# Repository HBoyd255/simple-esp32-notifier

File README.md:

# Simple ESP32 Notifier

This is just a simple board to hold a
[Heltec WiFi Kit 32](https://heltec.org/project/wifi-kit32-v3/) ESP32 dev kit.

The board works for either the V2 or V3 boards, but require different pin
definitions due to the different pinouts of the boards. Pin definitions can be
found in [pinDefs_V2.h](reference/pinDefs_V2.h) and
[pinDefs_V3.h](reference/pinDefs_V3.h).

This Heltec board comes with a built in 0.96 OLED screen that is used for
showing notifications, and the board adds 3 LEDs and 3 Buttons.

As this board is designed to be simple it just uses through hole components and
uses one GPIO pin per LED and one per button.

# Photos

## Credit

For the ESP I am using a library by [bartloeff](https://github.com/bartloeff)
titled [heltec_htit-wb32](https://github.com/bartloeff/heltec_htit-wb32)

## Metric

The board is 7cm tall and 6cm wide, with 5mm radius corners.

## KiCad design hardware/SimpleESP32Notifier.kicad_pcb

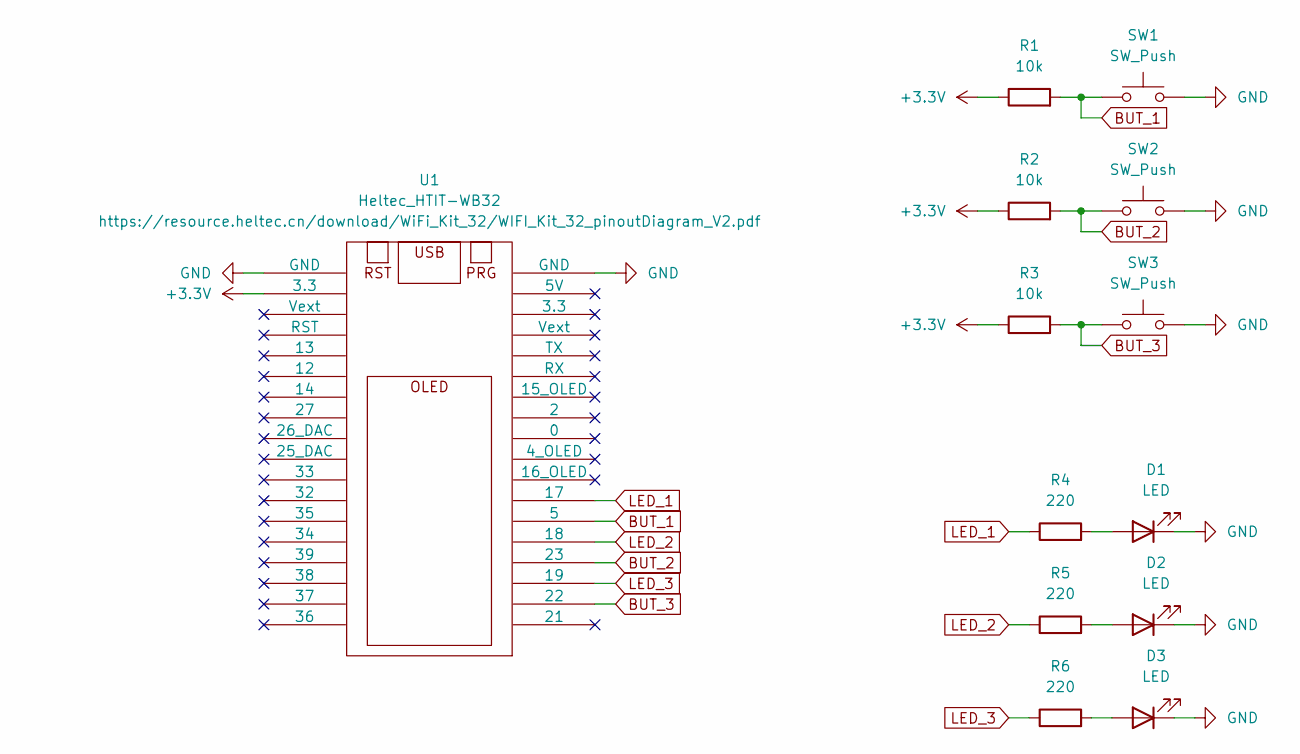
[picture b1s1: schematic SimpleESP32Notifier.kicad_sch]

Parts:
D1, D2, D3: LED; LED_D5.0mm
R1, R2, R3: 10k; R_Axial_DIN0207_L6.3mm_D2.5mm_P7.62mm_Horizontal
R4, R5, R6: 220; R_Axial_DIN0207_L6.3mm_D2.5mm_P7.62mm_Horizontal
SW1, SW2, SW3: SW_Push; SW_PUSH_6mm
U1: Heltec_HTIT-WB32

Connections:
+3.3V: R1.1, R2.1, R3.1, U1.9 (3.3)
BUT_1: R1.2, SW1.1, U1.5
BUT_2: R2.2, SW2.1, U1.23
BUT_3: R3.2, SW3.1, U1.22
GND: D1.1 (K), D2.1 (K), D3.1 (K), SW1.2, SW2.2, SW3.2, U1.8 (GND), U1.28 (GND)
LED_1: R4.1, U1.17
LED_2: R5.1, U1.18
LED_3: R6.1, U1.19
unnamed: D1.2 (A), R4.2
unnamed: D2.2 (A), R5.2
unnamed: D3.2 (A), R6.2

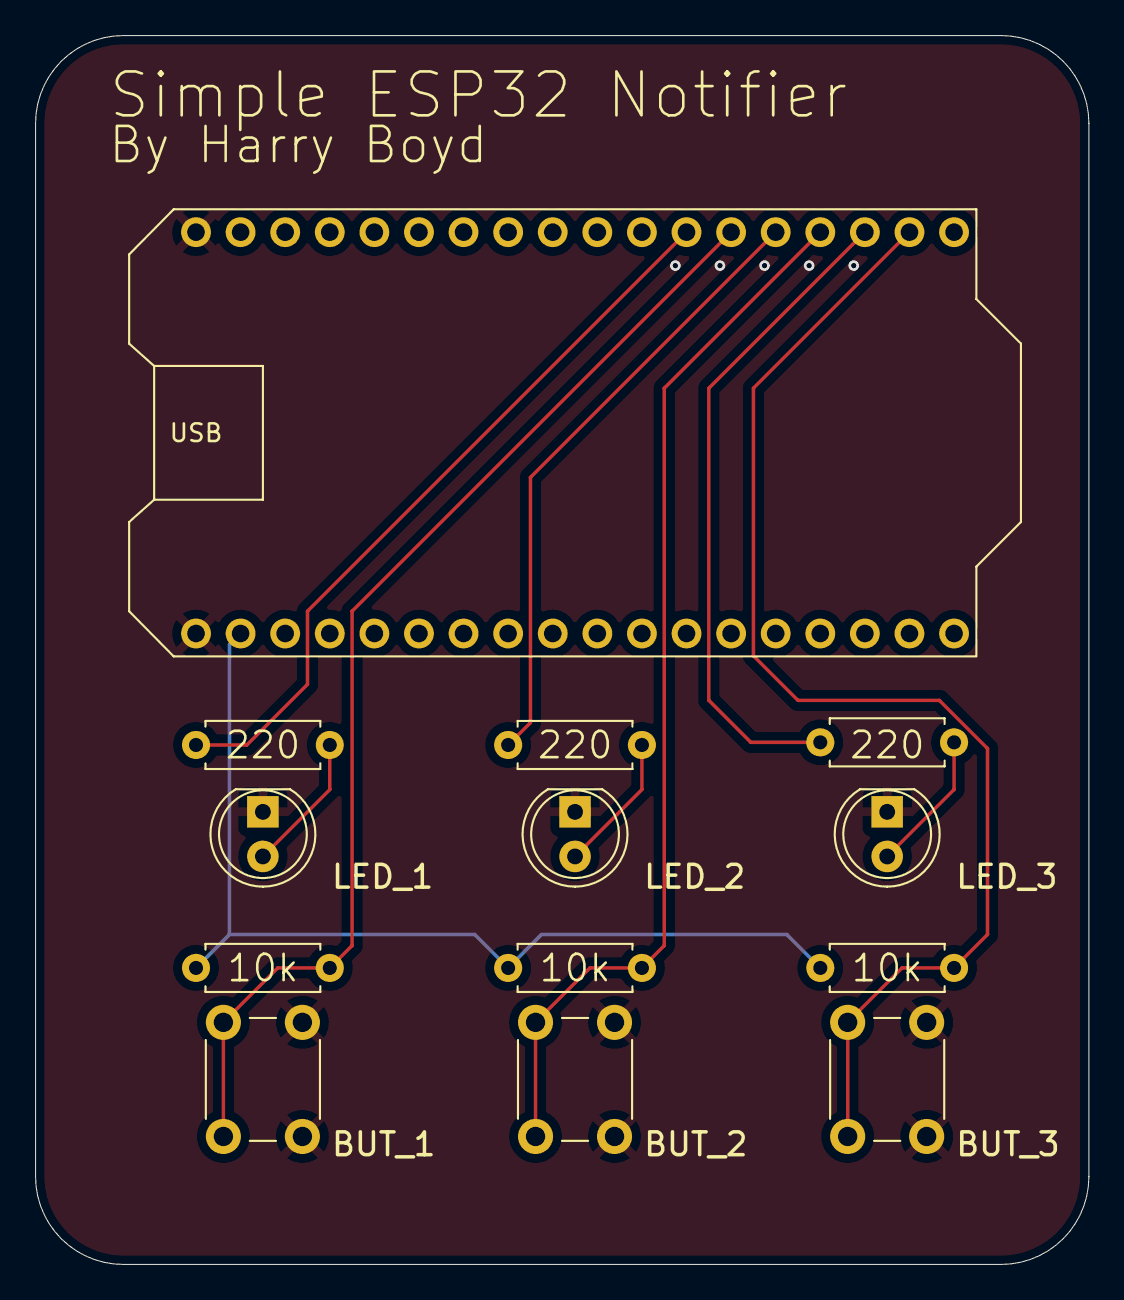
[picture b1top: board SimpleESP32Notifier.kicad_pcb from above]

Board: 2 copper layers, 60.0 x 70.0 mm, 13 parts (0 on the bottom side), 11 nets.

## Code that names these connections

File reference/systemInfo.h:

// This is a copy of the pin definitions for the robot.

#ifndef SYSTEM_INFO_H
#define SYSTEM_INFO_H

#define LED_1 17
#define LED_2 18
#define LED_3 19

#define BUT_1 5
#define BUT_2 23
#define BUT_3 22

#endif  // SYSTEM_INFO_H

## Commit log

2024-11-06 Created Repo
2024-11-06 Added esp32 library
2024-11-07 Decided layout
2024-11-07 Rounded corners
2024-11-07 Finished schematic
2024-11-07 Exported V1.0
2024-11-07 Fixed pins wiring of v1.0
2024-11-22 Added photos
